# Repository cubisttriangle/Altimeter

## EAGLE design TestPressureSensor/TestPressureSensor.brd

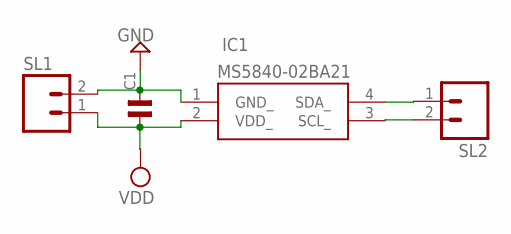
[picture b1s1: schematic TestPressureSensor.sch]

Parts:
C1: C0805; 0805
IC1: MS5840-02BA21; MS584002BA21
SL1, SL2: M02; 02P

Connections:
GND: C1.2, IC1.1 (GND_), SL1.2
unnamed: IC1.4 (SDA_), SL2.1
unnamed: IC1.3 (SCL_), SL2.2
VDD: C1.1, IC1.2 (VDD_), SL1.1

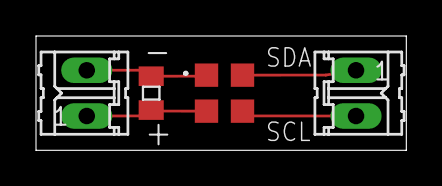
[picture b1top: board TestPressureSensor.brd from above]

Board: 2 copper layers, 20.6 x 6.3 mm, 4 parts (0 on the bottom side), 4 nets.

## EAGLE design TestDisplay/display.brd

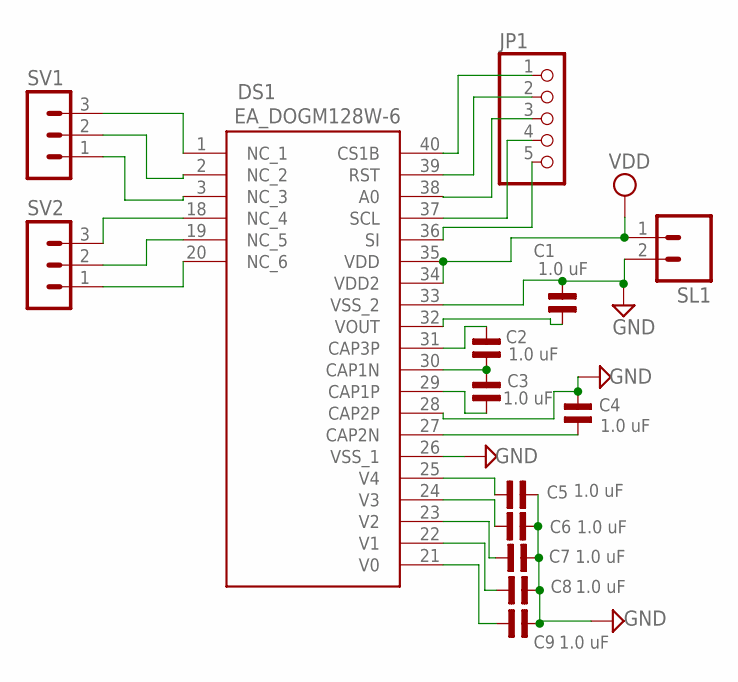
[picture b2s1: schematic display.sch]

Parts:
C1, C2, C3, C4, C5, C6, C7, C8, C9: 1.0 uF; 0805
DS1: EA_DOGM128W-6; EADOGM128W6
JP1: PINHD-1X5; 1X05
SL1: M02; 02P
SV1, SV2: MA03-1

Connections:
GND: C1.2, C4.2, C5.2, C6.2, C7.2, C8.2, C9.2, DS1.26 (VSS_1), DS1.28 (CAP2P), DS1.33 (VSS_2), SL1.2
unnamed: C2.1, C3.2, DS1.30 (CAP1N)
unnamed: C2.2, DS1.31 (CAP3P)
unnamed: C3.1, DS1.29 (CAP1P)
unnamed: DS1.36 (SI), JP1.5
unnamed: C4.1, DS1.27 (CAP2N)
unnamed: C5.1, DS1.25 (V4)
unnamed: C6.1, DS1.24 (V3)
unnamed: C7.1, DS1.23 (V2)
unnamed: C8.1, DS1.22 (V1)
unnamed: C9.1, DS1.21 (V0)
unnamed: DS1.20 (NC_6), SV2.1
unnamed: DS1.19 (NC_5), SV2.2
unnamed: C1.1, DS1.32 (VOUT)
unnamed: DS1.18 (NC_4), SV2.3
unnamed: DS1.3 (NC_3), SV1.1
unnamed: DS1.2 (NC_2), SV1.2
unnamed: DS1.1 (NC_1), SV1.3
unnamed: DS1.37 (SCL), JP1.4
unnamed: DS1.38 (A0), JP1.3
unnamed: DS1.39 (RST), JP1.2
unnamed: DS1.40 (CS1B), JP1.1
VDD: DS1.34 (VDD2), DS1.35 (VDD), SL1.1

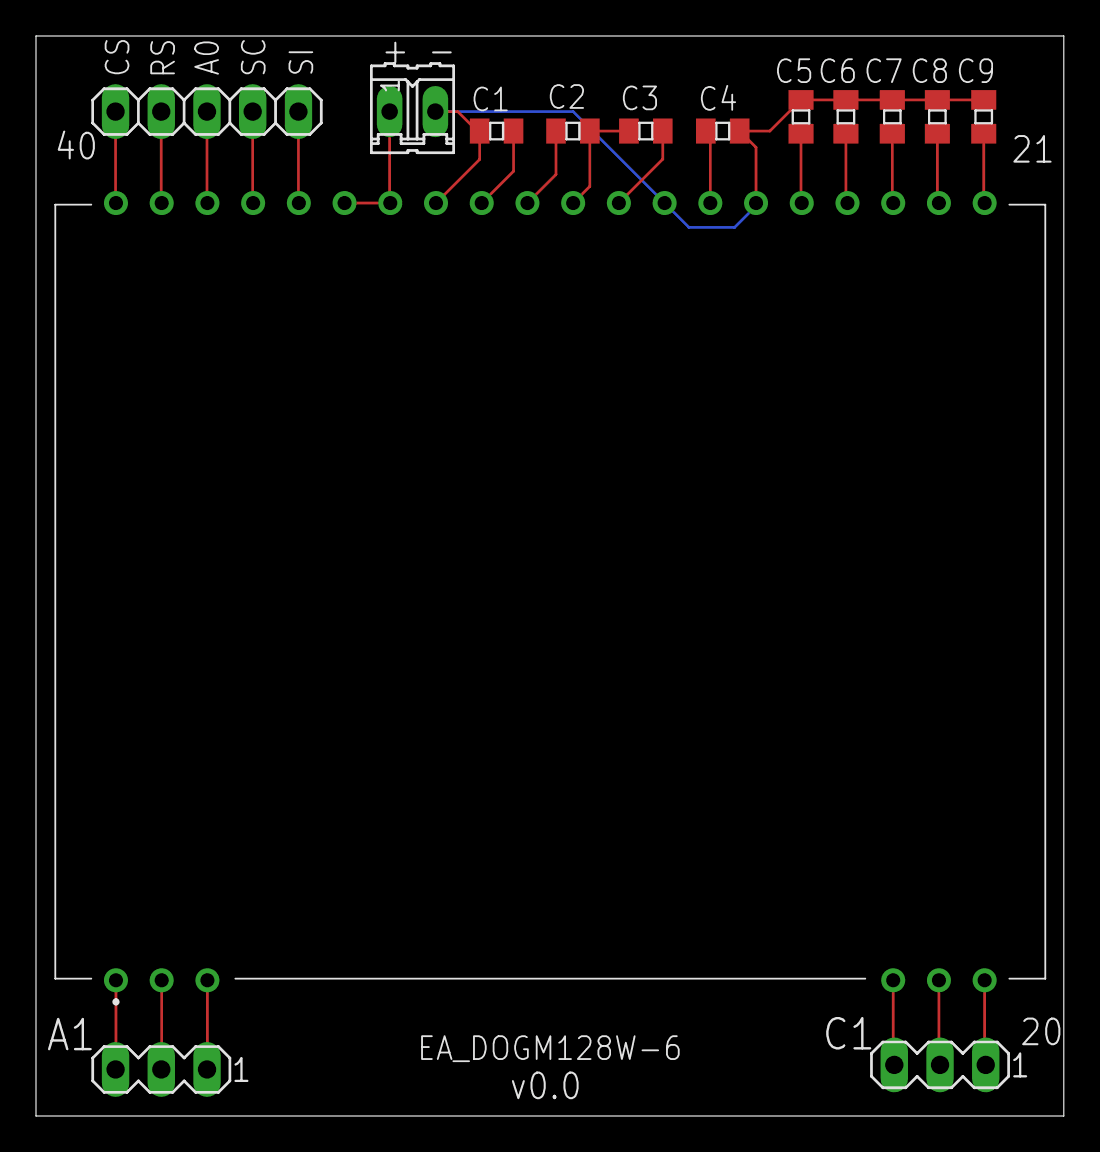
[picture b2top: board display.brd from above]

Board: 2 copper layers, 57.1 x 60.0 mm, 14 parts (0 on the bottom side), 23 nets.

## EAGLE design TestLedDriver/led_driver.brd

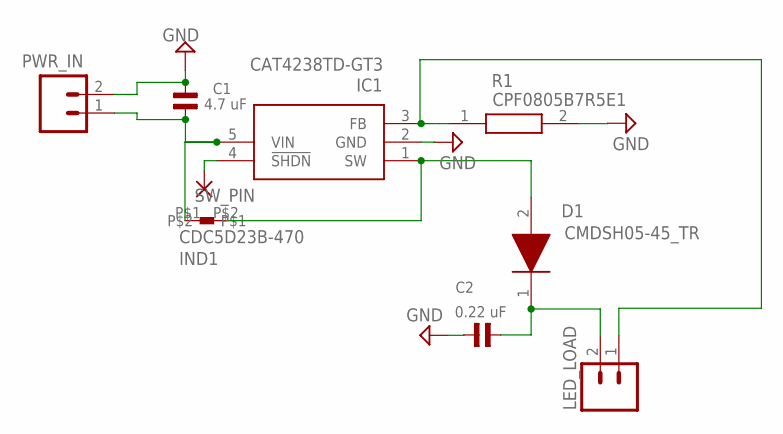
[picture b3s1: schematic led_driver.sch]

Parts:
C1: 4.7 uF; 0805
C2: 0.22 uF; 0805
D1: CMDSH05-45_TR; SOD2512X110N
IC1: CAT4238TD-GT3; SOT95P280X100-5N
IND1: CDC5D23B-470
LED_LOAD: M02; 02P
PWR_IN: M02; 02P
R1: CPF0805B7R5E1; RESC2012X65N
SW_PIN: 2,54/1,1

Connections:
GND: C1.2, C2.2, IC1.2 (GND), PWR_IN.2, R1.2
unnamed: C2.1, D1.1 (K), LED_LOAD.2
unnamed: IC1.4 (!SHDN), SW_PIN.1
unnamed: IC1.3 (FB), LED_LOAD.1, R1.1
SW: D1.2 (A), IC1.1 (SW), IND1.P$2
VIN: C1.1, IC1.5 (VIN), IND1.P$1, PWR_IN.1

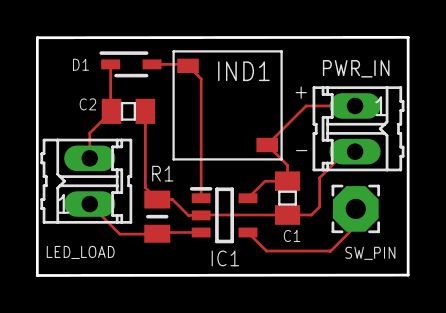
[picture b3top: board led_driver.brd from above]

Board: 2 copper layers, 20.6 x 13.2 mm, 9 parts (0 on the bottom side), 6 nets.

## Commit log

2020-11-13 Complete v0 of dislay test board.
2020-11-13 Add v0 test pressure sensor board/schematic.
